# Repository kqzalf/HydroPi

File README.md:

# HydroPi

## Overview
HydroPi is a project that uses a Raspberry Pi and Arduino to monitor environmental conditions using various sensors. The system logs sensor data and provides a web interface for viewing the data.

## Hardware List
- Arduino Uno R3
- Raspberry Pi 5
- Samsung 32GB EVO Plus Class 10 Micro SDHC
- diymore ph-4502c (pH sensor)
- tds meter v1.0
- Adafruit CCS811 Air Quality Sensor
- Gowoops DHT22 Temp/Humidity Sensor
- Adafruit TSL2591 Digital Light Sensor
- Autofocus for Raspberry Pi Camera
- DS18B20 Waterproof Temperature Sensor Probe Module
- Capacitive Soil Moisture Sensor

## Wiring Instructions
- **DHT22 (AM2302)**: 
  - + to 3V3 (Pin 1)
  - OUT to BCM 17 (Pin 11)
  - - to Ground (Pin 6)
- **TSL2591**:
  - VIN to 5V Power (Pin 2)
  - GND to Ground (Pin 6)
  - SDA to SDA (Pin 3)
  - SCL to SCL (Pin 5)
- **CCS811**:
  - VIN to 5V Power (Pin 4)
  - GND to Ground (Pin 14)
  - SDA to SDA (Pin 3)
  - SCL to SCL (Pin 5)
  - WAKE to Ground (Pin 20)

## Directory Structure
- `rev1/`
  - `arduino/`
    - `sensors/`
      - `pH_sensor/`
      - `tds_sensor/`
      - `water_temp_sensor/`
      - `analogue_soil_moisture_sensor/`
    - `HydropiSensorModule/`
  - `Pi/`
    - `Web/`
      - `mainSensors.php`
      - `auxSensors.php`
      - `functions.php`
      - `logSubmit.php`
      - `getPic.php`
      - `handle.php`
      - `index.php`
    - `Python/`
      - `sensors.py`
      - `Sense_v1.1.py`
      - `dashboard/`
        - `app.py`
        - `templates/`
          - `dashboard.html`
        - `requirements.txt`

## Setup Instructions
1. **Raspberry Pi Setup**:
   - Install required Python packages:
     ```bash
     sudo pip3 install Adafruit_DHT
     sudo apt-get install python-picamera python3-picamera python-rpi.gpio
     sudo pip3 install --upgrade picamera[array]
     sudo apt-get install python-opencv
     ```
   - Ensure the Arduino is connected to the Raspberry Pi via USB.

2. **Arduino Setup**:
   - Upload the appropriate Arduino sketches for each sensor.

## Usage Instructions
- Run the main sensing script:
  ```bash
  python3 Sense_v1.1.py
  ```
- The script will log sensor data to `/var/www/html/logs/mainlog.log`.

## Local Dashboard
A local dashboard is available to view the latest and historical sensor data. It runs on your Pi and is accessible at http://localhost:5000 or your Pi's IP address.

### Setup
1. Install Flask:
   ```bash
   pip3 install -r rev1/Pi/Python/dashboard/requirements.txt
   ```
2. Run the dashboard:
   ```bash
   python3 rev1/Pi/Python/dashboard/app.py
   ```

### Features
- Shows the latest sensor readings
- Displays a chart of the last 24 hours (up to 144 readings)
- Auto-refreshes every 10 seconds if new data is available
- Manual refresh button

## License
This project is licensed under the terms of the LICENSE file included in the repository.

## CI/CD
This project uses GitHub Actions for continuous integration. The workflow runs on every push and pull request to the `main` branch. It installs dependencies and runs tests using pytest.

## Linting
To ensure code quality, pylint is used for linting Python code. A `.pylintrc` file is included in the `rev1/Pi/Python/` directory to configure linting rules. Run the following command to lint the Python files:
```bash
pylint rev1/Pi/Python/*.py
```

## Testing
Tests are written using pytest and are located in `rev1/Pi/Python/test_sensors.py`. To run the tests, execute:
```bash
pytest rev1/Pi/Python/
```

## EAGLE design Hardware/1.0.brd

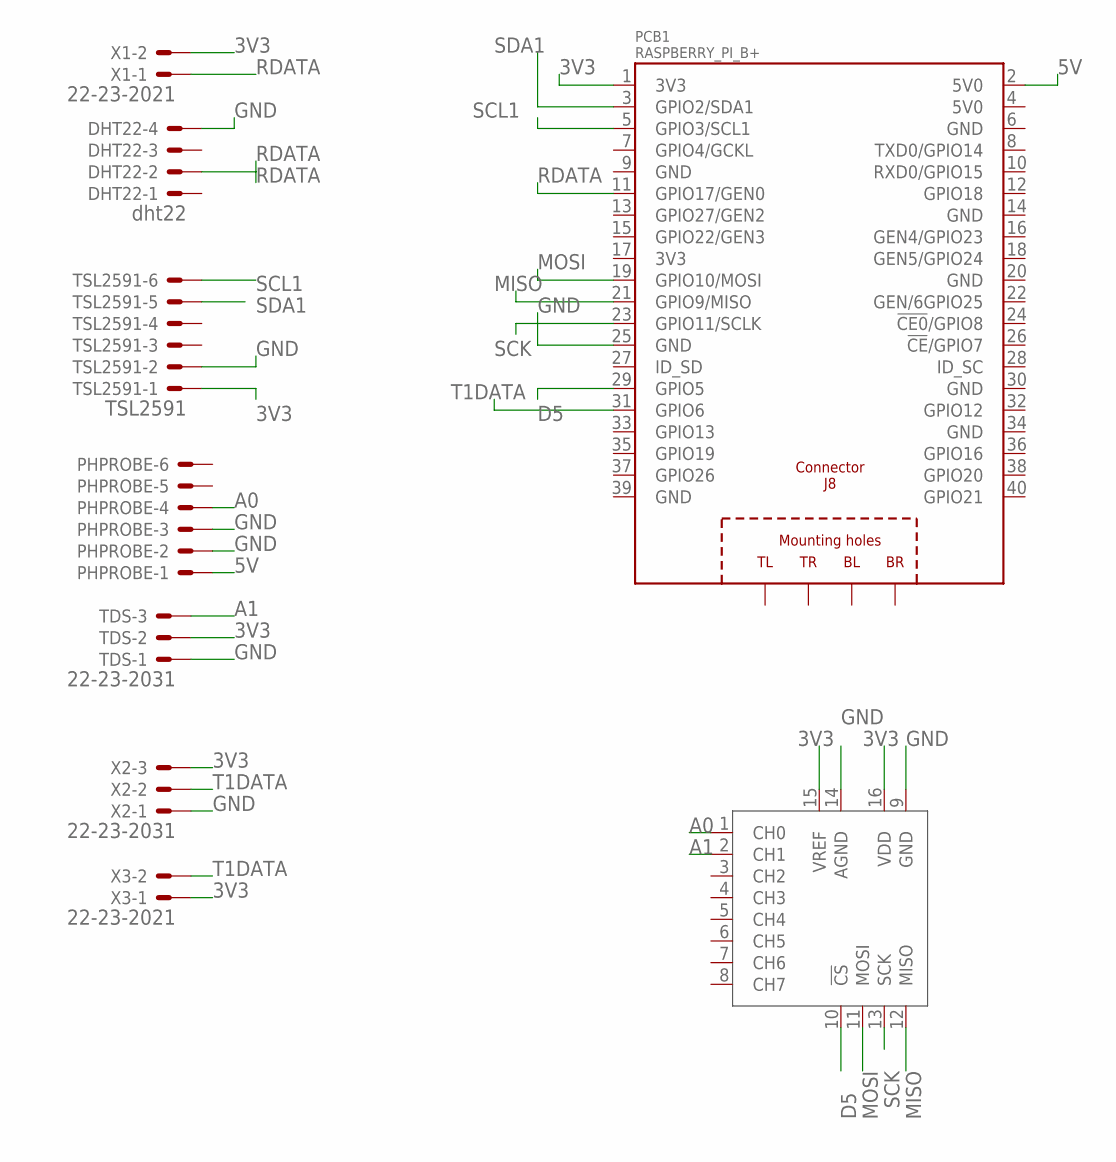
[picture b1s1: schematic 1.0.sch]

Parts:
DHT22: dht22; 22-23-2041
PCB1: RASPBERRY_PI_B+
PHPROBE: 22-23-2061
TDS: 22-23-2031
TSL2591: TSL2591; 22-23-2061
U$1: MCP3008P; DIL16
X1, X3: 22-23-2021
X2: 22-23-2031

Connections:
3V3: PCB1.1 (3V3), TDS.2, TSL2591.1, U$1.15 (VREF), U$1.16 (VDD), X1.2, X2.3, X3.1
5V: PCB1.2 (5V0), PHPROBE.1
A0: PHPROBE.4, U$1.1 (CH0)
A1: TDS.3, U$1.2 (CH1)
D5: PCB1.29 (GPIO5), U$1.10 (!CS)
GND: DHT22.4, PCB1.25 (GND), PHPROBE.2, PHPROBE.3, TDS.1, TSL2591.2, U$1.9 (GND), U$1.14 (AGND), X2.1
MISO: PCB1.21 (GPIO9/MISO), U$1.12 (MISO)
MOSI: PCB1.19 (GPIO10/MOSI), U$1.11 (MOSI)
RDATA: DHT22.2, PCB1.11 (GPIO17/GEN0), X1.1
SCK: PCB1.23 (GPIO11/SCLK), U$1.13 (SCK)
SCL1: PCB1.5 (GPIO3/SCL1), TSL2591.6
SDA1: PCB1.3 (GPIO2/SDA1), TSL2591.5
T1DATA: PCB1.31 (GPIO6), X2.2, X3.2

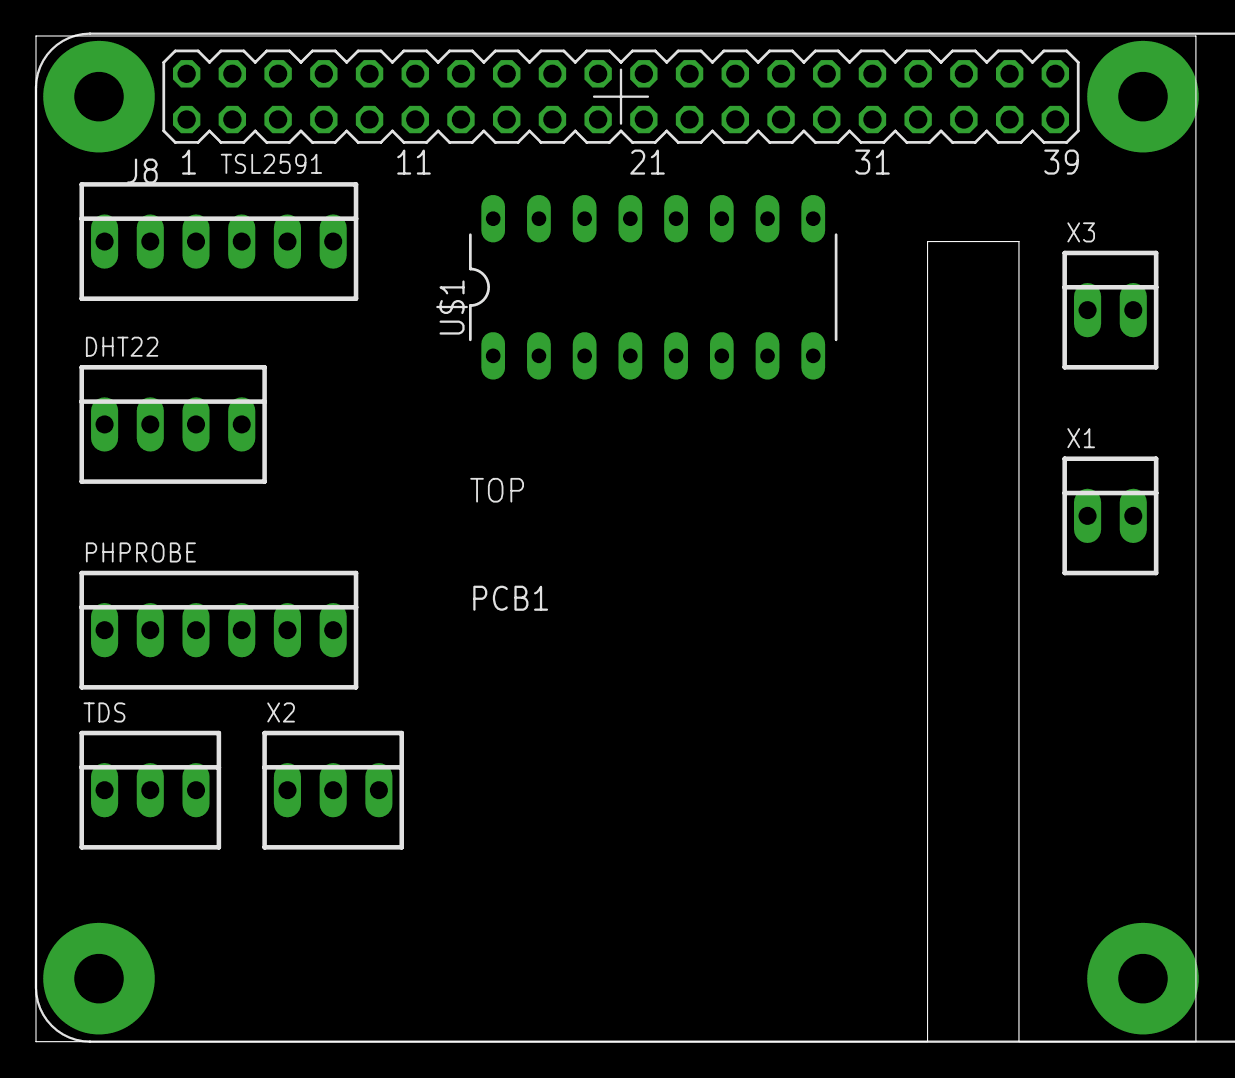
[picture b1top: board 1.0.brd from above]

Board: 2 copper layers, 64.4 x 55.9 mm, 9 parts (0 on the bottom side), 13 nets.

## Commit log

2019-11-18 uploading boards
2019-11-18 Add files via upload
    pH sensor Scripts
2019-11-19 Rename tempx.py to Python/tempx.py
2019-11-19 Create C#
2019-11-23 file orgonization
    cleaned up file structure. we are working on rev1 now
2019-11-24 Rename tempx.py to waterTemp.py
2019-11-24 Create part list
    list of hardware
2019-11-24 Update part list
2019-11-24 web monitor
2019-11-24 tds sensor done
    can plug water temp into this for more accuracy but its give or take 5ppm off
2019-11-26 Add files via upload
    it doesint read correctly every other read. change timer maybe, should not be an issue, just be aware of it.
2019-11-27 Add files via upload
    snaps images 5 sec wait, and enter/exit preview.
2019-12-02 code fix
    changed the dh22 code and library and added error checking
2019-12-04 added sense.py
    sense.py grabs the data from sensors,and writes it to a logfile that the web interface can read and use.
2019-12-05 xx
    xxx
2019-12-06 x
    x
2019-12-07 added wiering
2019-12-07 ddd
    dd
2019-12-07 Add files via upload
    This is the currently working script for our dht22 sensor. 12/7/19
2019-12-08 fix wiering diagram
    g
2019-12-08 works
    sss
2019-12-08 Add files via upload
    Now with time stamps for data reads. Change output as needed.
2019-12-09 Add files via upload
    executes sensor functions, and writes to a file. dependent on Functions.py (Must be in same folder)
2019-12-09 Add files via upload
    contains functions that run sensors, Sense_v1.0.py is dependent on this. (keep in same folder).
2019-12-09 Add files via upload
    truncates microseconds
2019-12-10 vvv
    vvv
2019-12-13 cleaning up
2019-12-14 overhauled the web interface
    functionized web interface and cleaned up everything
2019-12-14 cleaning up
    cleaning
2019-12-14 ff
    ff
2019-12-16 xx
    xx
2019-12-20 added functions.py
2025-05-21 refresh
2025-05-21 resgr
2025-05-21 vdszgf
2025-05-21 jhgfjy
2025-05-21 gfgf
2025-05-21 ;lkj
